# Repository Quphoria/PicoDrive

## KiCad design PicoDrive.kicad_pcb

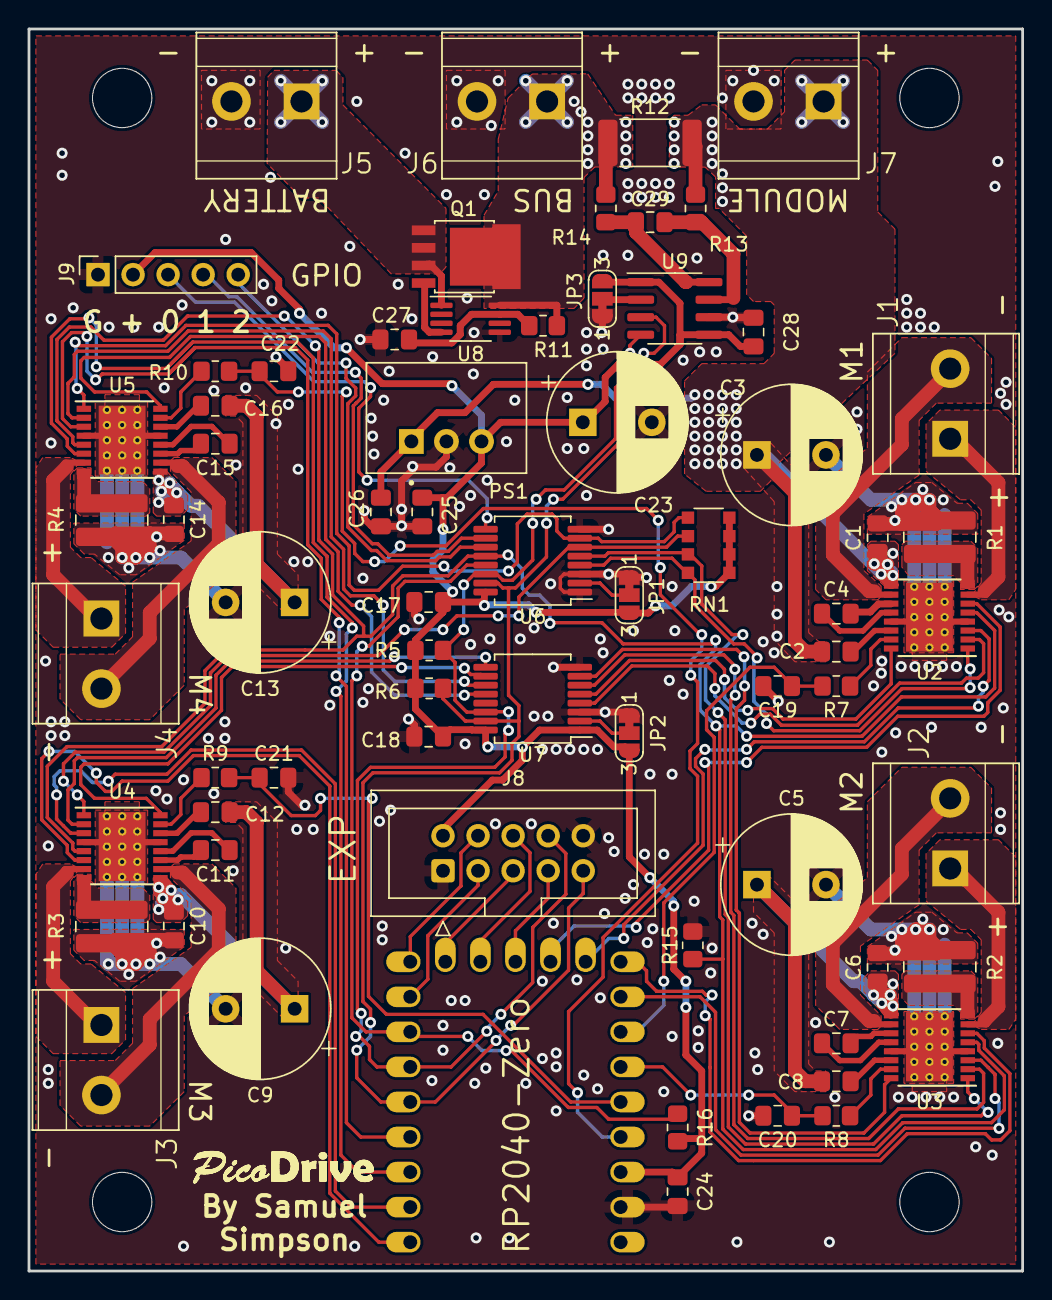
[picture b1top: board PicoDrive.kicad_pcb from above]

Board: 2 copper layers, 72.0 x 90.0 mm, 73 parts (0 on the bottom side), 76 nets.

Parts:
C1, C2, C4, C6, C7, C8, C10, C11, C12, C14, C15, C16, C17, C18, C24, C25, C26, C27, C28, C29: 0.1uF; C_0805_2012Metric_Pad1.18x1.45mm_HandSolder
C3, C5, C9, C13, C23: 100uF; CP_Radial_D10.0mm_P5.00mm
C19, C20, C21, C22: 1000pF; C_0805_2012Metric_Pad1.18x1.45mm_HandSolder
H1, H2, H3, H4: MountingHole; MountingHole_4.3mm_M4
J1, J2, J3, J4, J5, J6, J7: Conn_01x02; CUI_TB009-508-02BE
J8: Conn_02x05_Odd_Even; IDC-Header_2x05_P2.54mm_Vertical
J9: Conn_01x05; PinSocket_1x05_P2.54mm_Vertical
JP1, JP2, JP3: SolderJumper_3_Bridged12; SolderJumper-3_P1.3mm_Bridged12_RoundedPad1.0x1.5mm_NumberL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
PS1: P78E03-1000; CONV_P78E03-1000
Q1: PSMN4R5-30YLC; LFPAK56
R1, R2, R3, R4: 0.2; R_1020_2550Metric_Pad1.33x5.20mm_HandSolder
R5, R6: 1.65k; R_0805_2012Metric_Pad1.20x1.40mm_HandSolder
R7, R8, R9, R10, R15, R16: 10k; R_0805_2012Metric_Pad1.20x1.40mm_HandSolder
R11: 100; R_0805_2012Metric_Pad1.20x1.40mm_HandSolder
R12: 0.005; R_2512_6332Metric_Pad1.40x3.35mm_HandSolder
R13, R14: 10; R_0805_2012Metric_Pad1.20x1.40mm_HandSolder
RN1: 10k; R_Array_Convex_4x1206
U1: rp2040-zero; rp2040-zero-tht
U2, U3, U4, U5: DRV8801PWPR; HTSSOP-16-1EP_4.4x5mm_P0.65mm_EP3.4x5mm_Mask3x3mm_ThermalVi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
U6, U7: TCA9554DB; SSOP-16_5.3x6.2mm_P0.65mm
U8: LTC4357MS8; MSOP-8_3x3mm_P0.65mm
U9: INA219BIDR; SOIC-8_3.9x4.9mm_P1.27mm

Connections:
+3V3: C17.1, C18.1, C23.1, C24.2, C25.2, C28.1, J8.2, J9.2, JP1.3 (B), JP2.3 (B), JP3.3 (B), PS1.3 (+VOUT/GND), R5.2, R6.2, R16.2, RN1.1 (R1.1), RN1.2 (R2.1), RN1.3 (R3.1), RN1.4 (R4.1), U1.21 (3V3), U6.16 (VDD), U7.1 (A0), U7.16 (VDD), U9.1 (A1), U9.5 (VS)
+BATT: J5.1, Q1.1 (S), Q1.2 (S), Q1.3 (S), U8.1 (IN)
/EXP_IO_0: J9.3, U6.9 (P4)
/EXP_IO_1: J9.4, U6.10 (P5)
/EXP_IO_2: J9.5, U6.11 (P6)
/EXP_SCL: J8.8, R5.1, U1.6 (5), U6.14 (SCL), U7.14 (SCL), U9.4 (SCL)
/EXP_SDA: J8.9, R6.1, U1.5 (4), U6.15 (SDA), U7.15 (SDA), U9.3 (SDA)
/GPIO7: J8.3, U1.8 (7)
/GPIO8: J8.4, U1.9 (8)
/GPIO9: J8.5, U1.10 (9)
/GPIO10: J8.6, U1.11 (10)
/GPIO11: J8.7, U1.12 (11)
/M1_EN: U1.13 (12), U2.6 (ENABLE)
/M1_MODE1: U2.2 (MODE1), U7.4 (P0)
/M1_MODE2: U2.16 (MODE2), U7.5 (P1)
/M1_PH: U1.14 (13), U2.3 (PHASE)
/M1_VPROPI: C19.2, R7.1, U1.17 (26)
/M2_EN: U1.15 (14), U3.6 (ENABLE)
/M2_MODE1: U3.2 (MODE1), U7.6 (P2)
/M2_MODE2: U3.16 (MODE2), U7.7 (P3)
/M2_PH: U1.16 (15), U3.3 (PHASE)
/M2_VPROPI: C20.2, R8.1, U1.18 (27)
/M3_EN: U1.1 (0), U4.6 (ENABLE)
/M3_MODE1: U4.2 (MODE1), U7.9 (P4)
/M3_MODE2: U4.16 (MODE2), U7.10 (P5)
/M3_PH: U1.2 (1), U4.3 (PHASE)
/M3_VPROPI: C21.2, R9.1, U1.19 (28)
/M4_EN: U1.3 (2), U5.6 (ENABLE)
/M4_MODE1: U5.2 (MODE1), U7.11 (P6)
/M4_MODE2: U5.16 (MODE2), U7.12 (P7)
/M4_PH: U1.4 (3), U5.3 (PHASE)
/M4_VPROPI: C22.2, R10.1, U1.20 (29)
/Motor 1 Driver/OUT+: J1.1, U2.7 (OUT+)
/Motor 1 Driver/OUT-: J1.2, U2.10 (OUT-)
/Motor 1 Driver/SENSE: R1.1, U2.8 (SENSE)
/Motor 2 Driver/OUT+: J2.1, U3.7 (OUT+)
/Motor 2 Driver/OUT-: J2.2, U3.10 (OUT-)
/Motor 2 Driver/SENSE: R2.1, U3.8 (SENSE)
/Motor 3 Driver/OUT+: J3.1, U4.7 (OUT+)
/Motor 3 Driver/OUT-: J3.2, U4.10 (OUT-)
/Motor 3 Driver/SENSE: R3.1, U4.8 (SENSE)
/Motor 4 Driver/OUT+: J4.1, U5.7 (OUT+)
/Motor 4 Driver/OUT-: J4.2, U5.10 (OUT-)
/Motor 4 Driver/SENSE: R4.1, U5.8 (SENSE)
/~EXP1_INT: R16.1, U1.7 (6), U6.13 (~INT)
/~M1_FAULT: RN1.8 (R1.2), U2.1 (~FAULT), U6.4 (P0)
/~M2_FAULT: RN1.7 (R2.2), U3.1 (~FAULT), U6.5 (P1)
/~M3_FAULT: RN1.6 (R3.2), U4.1 (~FAULT), U6.6 (P2)
/~M4_FAULT: RN1.5 (R4.2), U5.1 (~FAULT), U6.7 (P3)
/~M_SLEEP: R15.1, U2.5 (~SLEEP), U3.5 (~SLEEP), U4.5 (~SLEEP), U5.5 (~SLEEP), U6.12 (P7)
GND1: C1.1, C3.2, C5.2, C6.1, C9.2, C10.1, C13.2, C14.1, C17.2, C18.2, C19.1, C20.1, C21.1, C22.1, C23.2, C24.1, C25.1, C26.2, C27.1, C28.2, J5.2, J6.2, J7.2, J8.1, J8.10, J9.1, JP1.1 (A), JP2.1 (A), JP3.1 (A), PS1.2 (GND/-VOUT), R1.2, R2.2, R3.2, R4.2, R15.2, U1.22 (GND), U2.4 (GND), U2.13 (GND), U2.17 (GND(PPAD)), U3.4 (GND), U3.13 (GND), U3.17 (GND(PPAD)), U4.4 (GND), U4.13 (GND), U4.17 (GND(PPAD)), U5.4 (GND), U5.13 (GND), U5.17 (GND(PPAD)), U6.1 (A0), U6.3 (A2), U6.8 (GND), U7.3 (A2), U7.8 (GND), U8.5 (GND), U9.6 (GND)
unnamed: JP1.2 (C), U6.2 (A1)
unnamed: JP2.2 (C), U7.2 (A1)
unnamed: JP3.2 (C), U9.2 (A0)
unnamed: Q1.4 (G), U8.4 (GATE)
unnamed: C4.2, U2.11 (CP1)
unnamed: C4.1, U2.12 (CP2)
unnamed: C2.2, U2.14 (VCP)
unnamed: R7.2, U2.15 (VPROPI)
unnamed: C7.2, U3.11 (CP1)
unnamed: C7.1, U3.12 (CP2)
unnamed: C8.2, U3.14 (VCP)
unnamed: R8.2, U3.15 (VPROPI)
unnamed: C11.2, U4.11 (CP1)
unnamed: C11.1, U4.12 (CP2)
unnamed: C12.2, U4.14 (VCP)
unnamed: R9.2, U4.15 (VPROPI)
unnamed: C15.2, U5.11 (CP1)
unnamed: C15.1, U5.12 (CP2)
unnamed: C16.2, U5.14 (VCP)
unnamed: R10.2, U5.15 (VPROPI)
unnamed: C27.2, R11.1, U8.7 (Vdd)
unnamed: C29.1, R14.2, U9.8 (IN+)
unnamed: C29.2, R13.2, U9.7 (IN-)
VBUS: J6.1, Q1.5 (D), R11.2, R12.1, R14.1, U8.8 (OUT)
Vdrive: C1.2, C2.1, C3.1, C5.1, C6.2, C8.1, C9.1, C10.2, C12.1, C13.1, C14.2, C16.1, C26.1, J7.1, PS1.1 (+VIN), R12.2, R13.1, U2.9 (VBB), U3.9 (VBB), U4.9 (VBB), U5.9 (VBB)

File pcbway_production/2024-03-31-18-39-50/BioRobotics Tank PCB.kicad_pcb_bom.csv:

designator,quantity,value,pack,mpn,mount_type
"C1, C10, C11, C12, C14, C15, C16, C17, C18, C2, C24, C25, C26, C27, C28, C29, C4, C6, C7, C8",20,0.1uF,C_0805_2012Metric_Pad1.18x1.45mm_HandSolder,,smt
"C13, C23, C3, C5, C9",5,100uF,CP_Radial_D10.0mm_P5.00mm,,tht
"C19, C20, C21, C22",4,1000pF,C_0805_2012Metric_Pad1.18x1.45mm_HandSolder,,smt
"H1, H2, H3, H4",4,MountingHole,MountingHole_4.3mm_M4,,tht
"J1, J2, J3, J4, J5, J6, J7",7,Conn_01x02,CUI_TB009-508-02BE,,tht
J8,1,Conn_02x05_Odd_Even,IDC-Header_2x05_P2.54mm_Vertical,,tht
J9,1,Conn_01x05,PinSocket_1x05_P2.54mm_Vertical,,tht
"JP1, JP2, JP3",3,SolderJumper_3_Bridged12,SolderJumper-3_P1.3mm_Bridged12_RoundedPad1.0x1.5mm_NumberLabels,,tht
PS1,1,P78E03-1000,CONV_P78E03-1000,,tht
Q1,1,IPD060N03LGATMA1,IPD060N03LGATMA1,,smt
"R1, R2, R3, R4",4,0.2,R_1020_2550Metric_Pad1.33x5.20mm_HandSolder,,smt
"R10, R15, R7, R8, R9",5,10k,R_0805_2012Metric_Pad1.20x1.40mm_HandSolder,,smt
R11,1,100,R_0805_2012Metric_Pad1.20x1.40mm_HandSolder,,smt
R12,1,0.005,R_2512_6332Metric_Pad1.40x3.35mm_HandSolder,,smt
"R13, R14",2,10,R_0805_2012Metric_Pad1.20x1.40mm_HandSolder,,smt
"R5, R6",2,1.65k,R_0805_2012Metric_Pad1.20x1.40mm_HandSolder,,smt
RN1,1,10k,R_Array_Convex_4x1206,,smt
U1,1,rp2040-zero,rp2040-zero-tht,,tht
"U2, U3, U4, U5",4,DRV8801PWP,HTSSOP-16-1EP_4.4x5mm_P0.65mm_EP3.4x5mm_Mask3x3mm_ThermalVias,,smt
"U6, U7",2,TCA9554DB,SSOP-16_5.3x6.2mm_P0.65mm,,smt
U8,1,LTC4357MS8,MSOP-8_3x3mm_P0.65mm,,smt
U9,1,INA219BIDR,SOIC-8_3.9x4.9mm_P1.27mm,,smt

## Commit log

2024-03-30 Add kleeb to git submodules
2024-03-31 Add 10k pulldown to nSleep and export BOM
2024-03-31 Update 0.1uF capacitor mfr no
2024-03-31 Change to product number to PCBWays template
2024-03-31 Move some silkscreen items
2024-03-31 Change Screw Terminal Part and update Mfr No's
2024-03-31 Increase DC-DC converter pad size
2024-03-31 Increase Mosfet pad size
2024-03-31 Generate PCBWay production files
2024-04-01 Change ideal diode mosfet and increase track sizes
2024-04-01 Remove unused kicad library
2024-04-01 Add via's around power connectors to improve current capacity
2024-04-01 Increase ground connection trace to motor drivers
2024-04-01 Copy extra ground trace for drivers to top layer
2024-04-01 Move some via's to improve routing / ground width
2024-04-01 Improve ground connection over Vdrive trace
2024-04-02 Add mouser no's, pullup resistor, change project name
2024-04-17 Fix io expander component to match footprint
2024-04-17 Fix mfault pullup resistor (it was configured as a pulldown)
2026-04-18 Add some pictures
